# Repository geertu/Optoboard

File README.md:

# optoboard
8-Channel Opto-Isolator Board for Board Farm Control

This is a small board to drive eight opto-isolators from an i2c GPIO expander,
to be connected to the i2c bus of an embedded board.

I designed this board to interact remotely with the various devices in my board
farm.  It is used to control system reset, system wake-up, and soft power-on
for the individual boards, and to power on/off the board farm main power supply
(power to the individual boards is controlled differently).

Of course it can be used to mimic keypresses or deliver "open collector" (or
emitter) signals in other projects.

Please see my presentation "Herd Your Boards, Become a Farmer" at the Embedded
Linux Conference Europe 2016 for more information:
  - https://elinux.org/images/b/b5/Herd_Your_Boards.pdf
  - https://www.youtube.com/watch?v=kwqmjeqAx-E

Noteworthy slides:
  - Slide 25 contains the rationale behind using optocouplers,
  - Slide 26 shows v1 of the board (on protoboard),
  - Slide 40-42 show the "software setup".

License: CC-BY-SA-4.0 (https://creativecommons.org/licenses/by-sa/4.0/)

PCB and parts can be ordered at https://aisler.net/geert/optoboard/optoboard
(Disclaimer: I'm not affiliated to AISLER)

Bill Of Materials:
  - C1: Capacitor, 100 nF, SMD 0805/2012
  - D1-D9: LED, SMD 0805/2012, e.g. Würth Elektronik 150080YS75000
  - P1-P2: 4-pin header, RM 2mm, e.g. JST B4B-PH-K
  - P3: Male or female 2x8 header, RM 2.54mm
  - R1-R2: Resistor, 4.7kΩ, SMD 0805/2012
    Note: These are pull-up resistors for the i2c bus.
          Populate only when needed (i.e. one or two sets per bus).
  - R3-R10: Resistor, 1kΩ, SMD 0805/2012
  - R11-R18: Resistor, 220Ω, SMD 0805/2012
  - R19: Resistor, 1kΩ, SMD 0805/2012
  - U1: I2C I/O expander, PCF8574DWR, SOIC-16
  - U2-U9: Opto-isolator, HCPL-181, Mini-Flat-4, e.g. Broadcom HCPL-181-00CE

For i2c cables:
  - 4-pin housings, RM 2mm, e.g. JST PHR-4
  - Crimp contacts, e.g. JST 800113
  - Wire

Connector pinouts:
  - P1 / P2: I2C input and output (for daisy-chaining)
      1. GND
      2. +3.3V
      3. SDA
      4. SCL
    Note: Pin order is similar to the Seeed Studio Grove and SparkFun Qwiic
          Connect systems, although the connector used is different (you can
	  probably mount a real Grove connector instead).

  - P3:
      1-15 (odd pins): Opto-isolator emitter ("negative output")
      2-16 (even pins): Opto-isolator collector ("positive output")

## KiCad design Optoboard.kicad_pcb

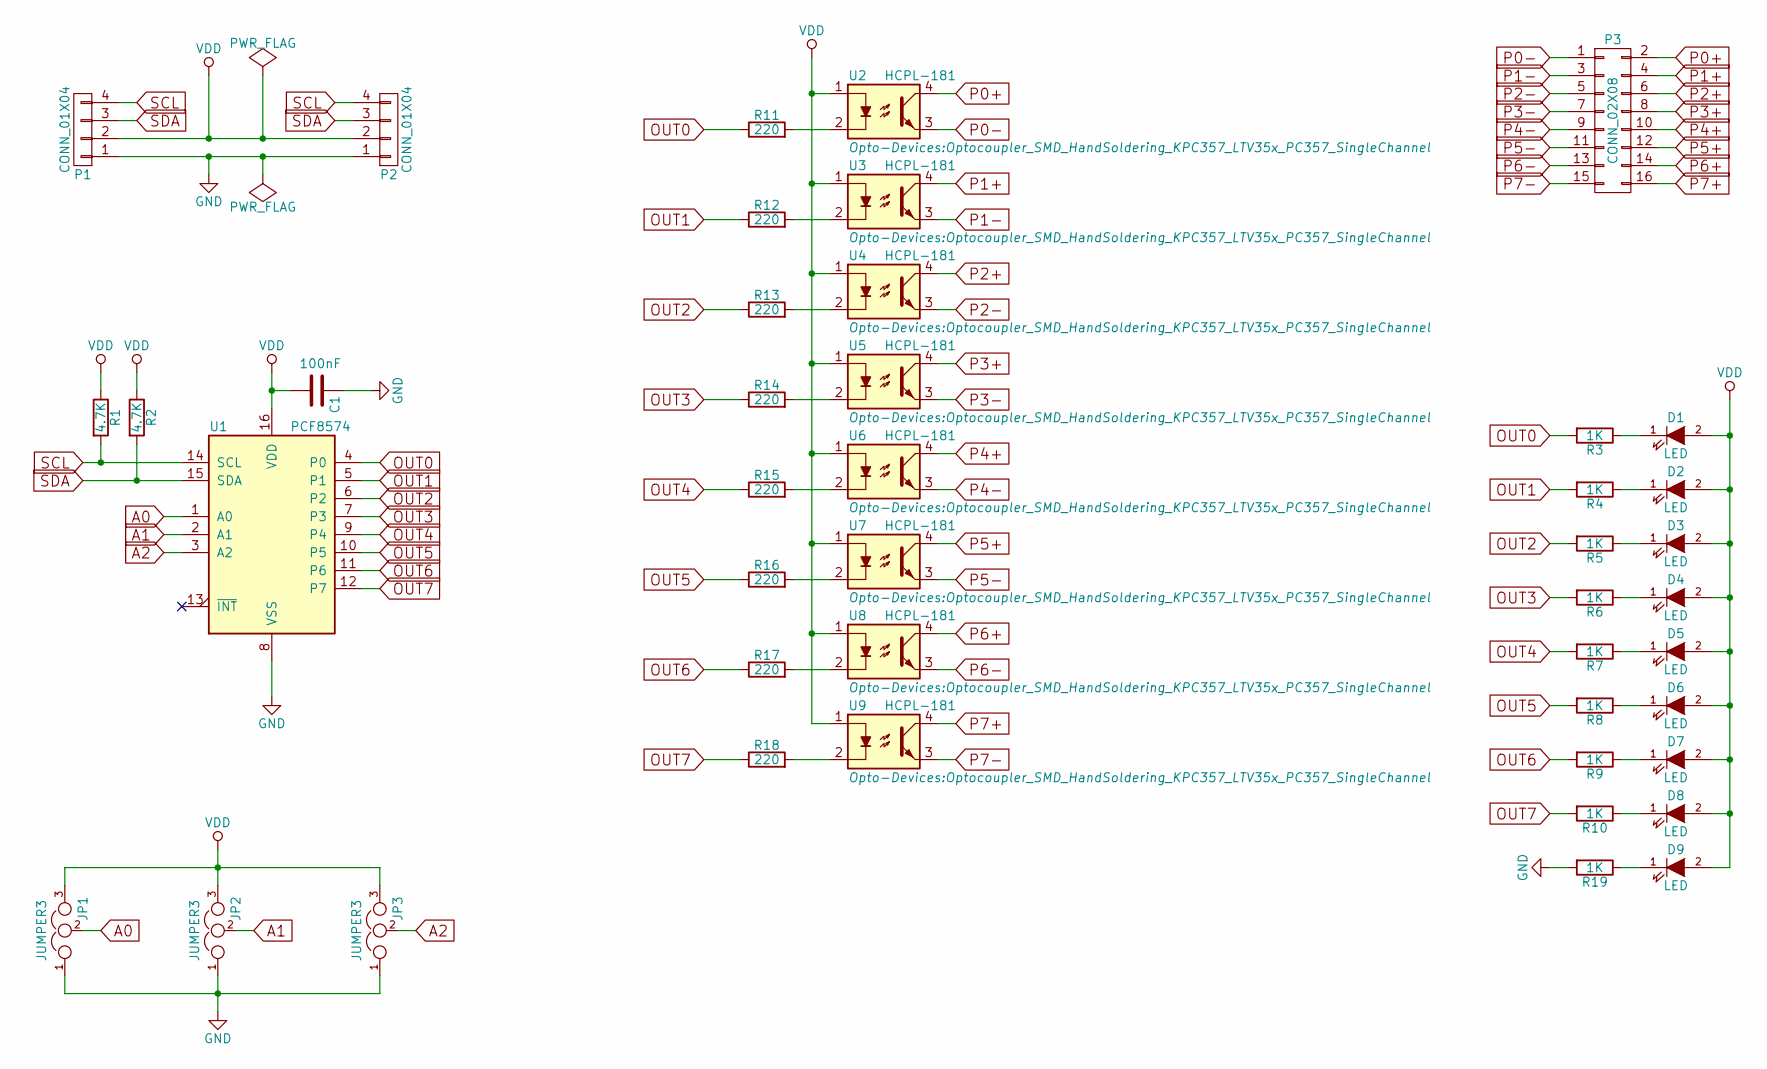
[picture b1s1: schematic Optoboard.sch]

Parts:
C1: 100nF; C_0805_HandSoldering
D1, D2, D3, D4, D5, D6, D7, D8, D9: LED; LED_0805
JP1, JP2, JP3: JUMPER3; GS3
P1, P2: CONN_01X04; Connectors_JST_B4B-PH-K
P3: CONN_02X08; Pin_Header_Straight_2x08
R1, R2: 4.7K; R_0805_HandSoldering
R3, R4, R5, R6, R7, R8, R9, R10, R19: 1K; R_0805_HandSoldering
R11, R12, R13, R14, R15, R16, R17, R18: 220; R_0805_HandSoldering
U1: PCF8574; SOIC-16_7.5x10.3mm_Pitch1.27mm
U2, U3, U4, U5, U6, U7, U8, U9: HCPL-181; Optocoupler_SMD_HandSoldering_KPC357_LTV35x_PC357_SingleCha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

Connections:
A0: JP1.2, U1.1 (A0)
A1: JP2.2, U1.2 (A1)
A2: JP3.2, U1.3 (A2)
GND: C1.1, JP1.1, JP2.1, JP3.1, P1.1, P2.1, R19.2, U1.8 (VSS)
unnamed: D1.1 (K), R3.1
unnamed: D2.1 (K), R4.1
unnamed: D3.1 (K), R5.1
unnamed: D4.1 (K), R6.1
unnamed: D5.1 (K), R7.1
unnamed: D6.1 (K), R8.1
unnamed: D7.1 (K), R9.1
unnamed: D8.1 (K), R10.1
unnamed: D9.1 (K), R19.1
unnamed: R11.2, U2.2
unnamed: R12.2, U3.2
unnamed: R13.2, U4.2
unnamed: R14.2, U5.2
unnamed: R15.2, U6.2
unnamed: R16.2, U7.2
unnamed: R17.2, U8.2
unnamed: R18.2, U9.2
OUT0: R3.2, R11.1, U1.4 (P0)
OUT1: R4.2, R12.1, U1.5 (P1)
OUT2: R5.2, R13.1, U1.6 (P2)
OUT3: R6.2, R14.1, U1.7 (P3)
OUT4: R7.2, R15.1, U1.9 (P4)
OUT5: R8.2, R16.1, U1.10 (P5)
OUT6: R9.2, R17.1, U1.11 (P6)
OUT7: R10.2, R18.1, U1.12 (P7)
P0+: P3.2, U2.4
P0-: P3.1, U2.3
P1+: P3.4, U3.4
P1-: P3.3, U3.3
P2+: P3.6, U4.4
P2-: P3.5, U4.3
P3+: P3.8, U5.4
P3-: P3.7, U5.3
P4+: P3.10, U6.4
P4-: P3.9, U6.3
P5+: P3.12, U7.4
P5-: P3.11, U7.3
P6+: P3.14, U8.4
P6-: P3.13, U8.3
P7+: P3.16, U9.4
P7-: P3.15, U9.3
SCL: P1.4, P2.4, R1.2, U1.14 (SCL)
SDA: P1.3, P2.3, R2.2, U1.15 (SDA)
VDD: C1.2, D1.2 (A), D2.2 (A), D3.2 (A), D4.2 (A), D5.2 (A), D6.2 (A), D7.2 (A), D8.2 (A), D9.2 (A), JP1.3, JP2.3, JP3.3, P1.2, P2.2, R1.1, R2.1, U1.16 (VDD), U2.1, U3.1, U4.1, U5.1, U6.1, U7.1, U8.1, U9.1

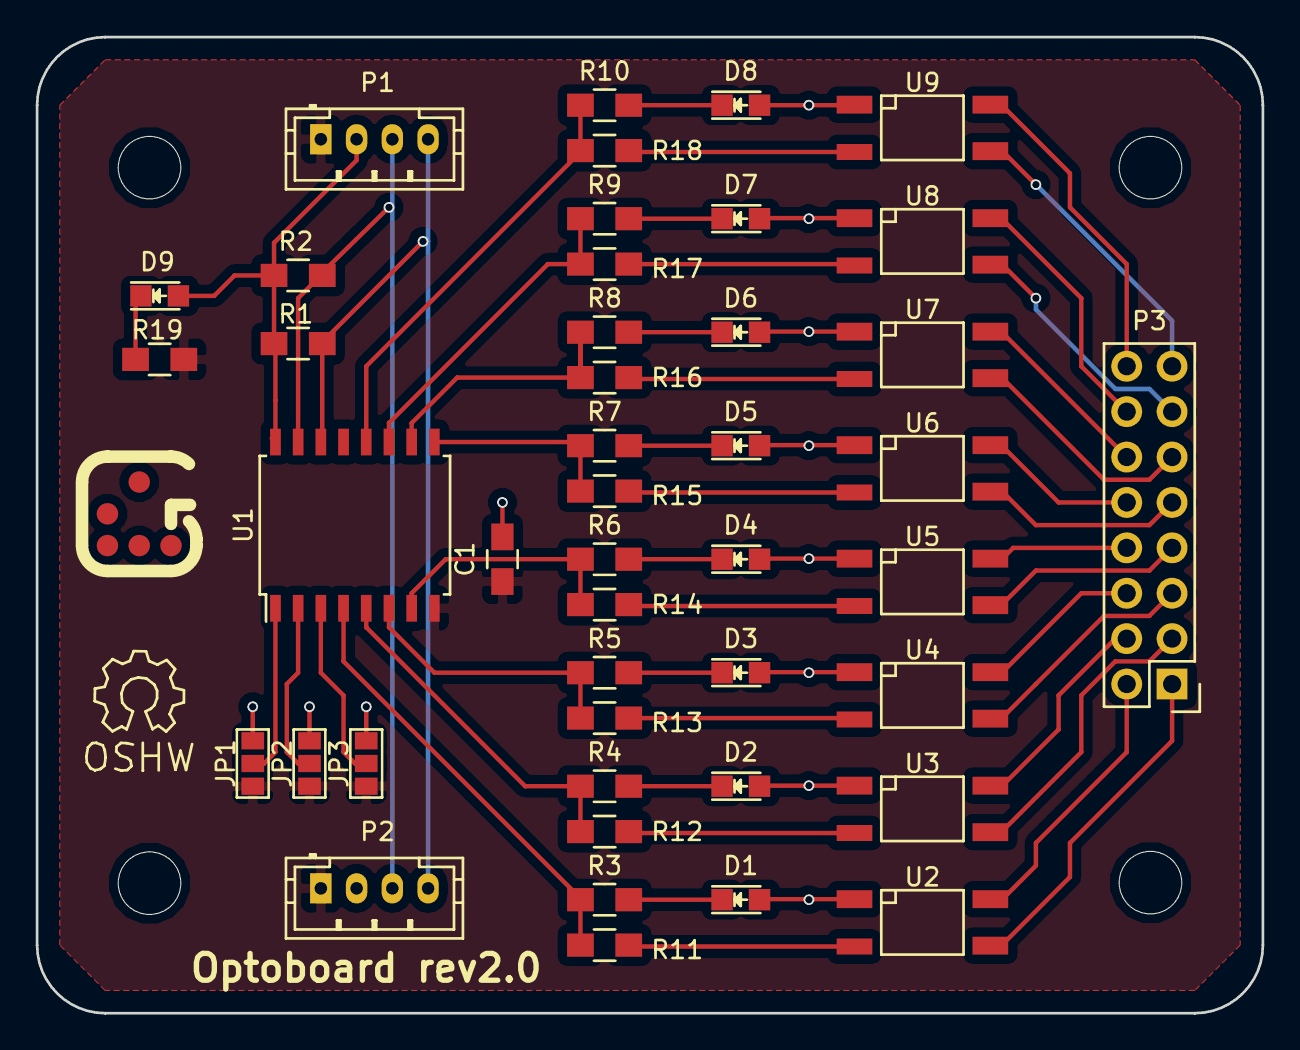
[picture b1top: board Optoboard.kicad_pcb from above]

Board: 2 copper layers, 68.6 x 54.6 mm, 50 parts (0 on the bottom side), 48 nets.

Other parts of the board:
Glider: Glider logo; Glider_bvba_G_Medium
Hole 1, Hole 2, Hole 3, Hole 4: MountingHole_3-5mm
OSHW: Symbol_OSHW-Logo_SilkScreen

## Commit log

2017-10-17 Add description and license
2017-10-17 Import KiCad design files
2017-10-17 Add link to project at AISLER
2017-11-28 Add Bill Of Materials
    Incl. i2c cables.
2017-11-28 Document connector pinouts
2018-10-01 Update board name at aisler.net
    The board is now called "optoboard" instead of the non-descriptive
    default "main-pcb".
